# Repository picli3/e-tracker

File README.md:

# e-track

E-paper based GPS tracker PCB design using KiCad.

## Project Structure

- `e-track.kicad_pcb` - Main PCB layout
- `e-track.kicad_sch` - Schematic file
- `e-track.kicad_pro` - KiCad project file
- `e-track.kicad_prl` - KiCad layout settings
- `Power_Manager.kicad_sch` - Power management module
- `e-paper.kicad_sch` - E-paper display module
- `docs/` - Datasheets and documentation

## Features

- E-paper display interface
- GPS module integration
- Power management system

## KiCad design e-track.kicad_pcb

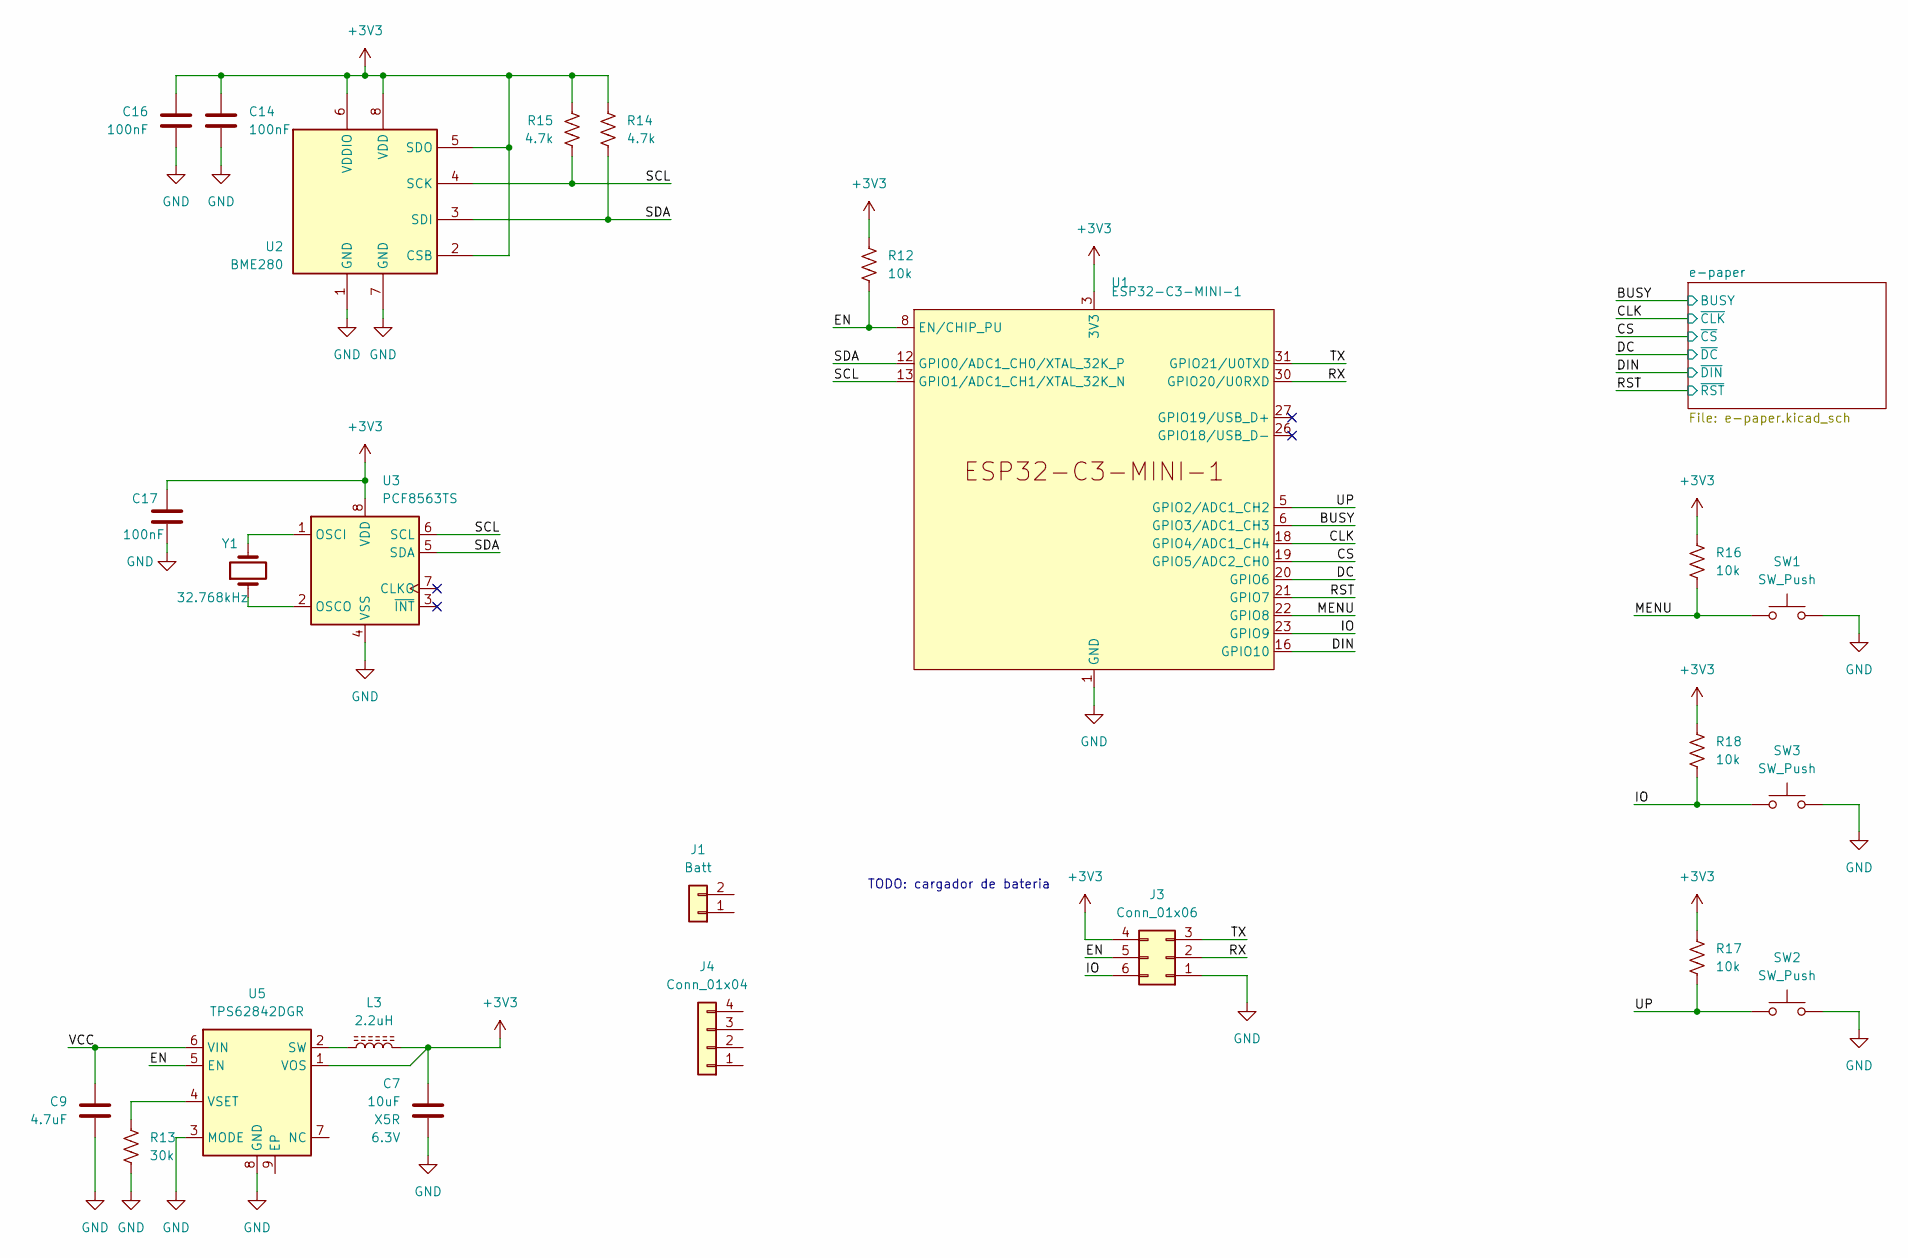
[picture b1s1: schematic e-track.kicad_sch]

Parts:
C7: 10uF; C_0805_2012Metric_Pad1.18x1.45mm_HandSolder; Mfr. Part CL21A106KPFNNNE; LCSC Part C17024
C9: 4.7uF; C_0603_1608Metric_Pad1.08x0.95mm_HandSolder; Mfr. Part CL10A475KP8NNNC; LCSC Part C1705
C14, C16, C17: 100nF; C_0603_1608Metric
J1: Batt; Samtec_UMPS-02-XX.X-X-V-S_1x02_P2.0mm_Socket
J3: Conn_01x06; pin-programmer
J4: Conn_01x04; pogo-pin-female-4P-2.54
L3: 2.2uH; L_Taiyo-Yuden_MD-4040; Mfr. Part LQH44PN2R2MP0L; LCSC Part C86081
R12, R16, R17, R18: 10k; R_0603_1608Metric
R13: 30k; R_0603_1608Metric_Pad0.98x0.95mm_HandSolder; Mfr. Part 0603WAF3002T5E; LCSC Part C22984
R14, R15: 4.7k; R_0603_1608Metric
SW1, SW2, SW3: SW_Push; SW_TL3340AF160QG
U1: ESP32-C3-MINI-1; ESP32-C3-MINI-1U
U2: BME280; Bosch_LGA-8_2.5x2.5mm_P0.65mm_ClockwisePinNumbering
U3: PCF8563TS; MSOP-8_3x3mm_P0.65mm; Part # PCF8563TS/5,118; LCSC C27397
U5: TPS62842DGR; MSOP-8-1EP_3x3mm_P0.65mm_EP1.5x1.8mm
Y1: 32.768kHz; Crystal_SMD_3215-2Pin_3.2x1.5mm; Part # SC-32S32.768kHz20PPM7pF; LCSC C97604

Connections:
+3V3: C7.1, C14.2, C16.2, C17.2, J3.4, L3.2, R12.2, R14.2, R15.2, R16.2, R17.2, R18.2, U1.3 (3V3), U2.2 (CSB), U2.5 (SDO), U2.6 (VDDIO), U2.8 (VDD), U3.8 (VDD), U5.1 (VOS); also elsewhere on the board
/BUSY: U1.6 (GPIO3/ADC1_CH3); also elsewhere on the board
/CLK: U1.18 (GPIO4/ADC1_CH4); also elsewhere on the board
/CS: U1.19 (GPIO5/ADC2_CH0); also elsewhere on the board
/DC: U1.20 (GPIO6); also elsewhere on the board
/DIN: U1.16 (GPIO10); also elsewhere on the board
/EN: J3.5, R12.1, U1.8 (EN/CHIP_PU), U5.5 (EN)
/IO: J3.6, R18.1, SW3.1, U1.23 (GPIO9)
/MENU: R16.1, SW1.1, U1.22 (GPIO8)
/RST: U1.21 (GPIO7); also elsewhere on the board
/RX: J3.2, U1.30 (GPIO20/U0RXD)
/SCL: R15.1, U1.13 (GPIO1/ADC1_CH1/XTAL_32K_N), U2.4 (SCK), U3.6 (SCL)
/SDA: R14.1, U1.12 (GPIO0/ADC1_CH0/XTAL_32K_P), U2.3 (SDI), U3.5 (SDA)
/TX: J3.3, U1.31 (GPIO21/U0TXD)
/UP: R17.1, SW2.1, U1.5 (GPIO2/ADC1_CH2)
/VCC: C9.1, U5.6 (VIN)
GND: C7.2, C9.2, C14.1, C16.1, C17.1, J3.1, R13.2, SW1.2, SW2.2, SW3.2, U1.1 (GND), U1.2 (GND), U1.11 (GND), U1.14 (GND), U1.36 (GND), U1.37 (GND), U1.38 (GND), U1.39 (GND), U1.40 (GND), U1.41 (GND), U1.42 (GND), U1.43 (GND), U1.44 (GND), U1.45 (GND), U1.46 (GND), U1.47 (GND), U1.48 (GND), U1.49 (GND), U1.50 (GND), U1.51 (GND), U1.52 (GND), U1.53 (GND), U2.1 (GND), U2.7 (GND), U3.4 (VSS), U5.3 (MODE), U5.8 (GND); also elsewhere on the board
unnamed: U3.1 (OSCI), Y1.2
unnamed: U3.2 (OSCO), Y1.1
unnamed: L3.1, U5.2 (SW)
unnamed: R13.1, U5.4 (VSET)

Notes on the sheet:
TODO: cargador de bateria

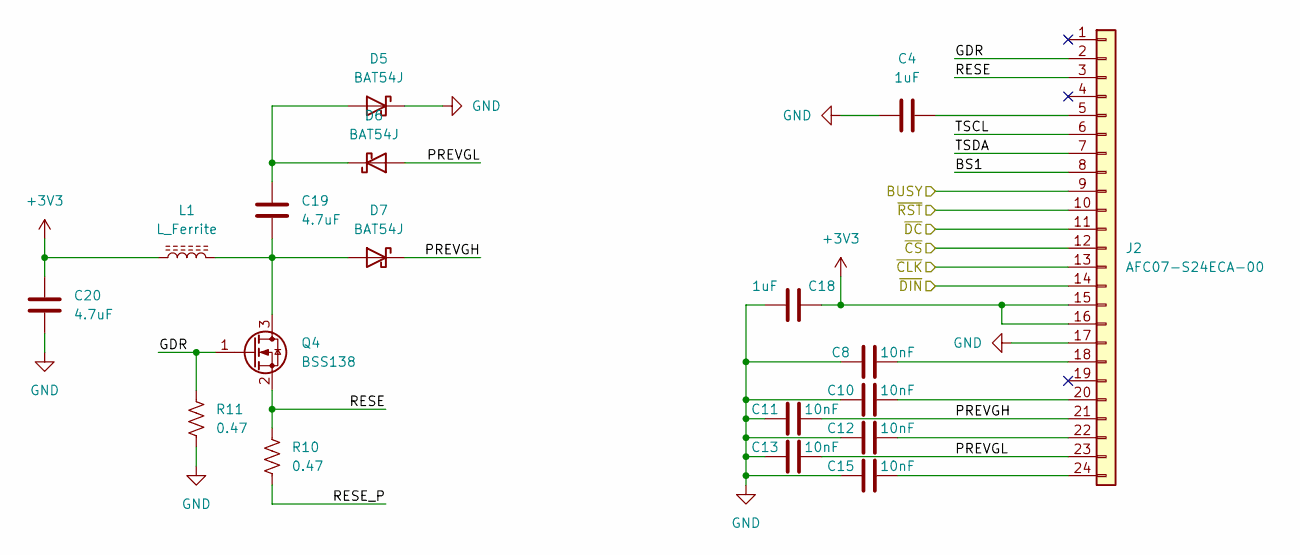
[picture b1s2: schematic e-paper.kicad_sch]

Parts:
C4, C18: 1uF; C_0603_1608Metric
C8, C10, C11, C12, C13, C15: 10nF; C_0603_1608Metric
C19, C20: 4.7uF; C_0603_1608Metric
D5, D6, D7: BAT54J; D_SOD-323F; LCSC C82046
J2: AFC07-S24ECA-00; TE_2-1734839-4_1x24-1MP_P0.5mm_Horizontal; Part # AFC07-S24ECA-00; LCSC C262643
L1: L_Ferrite; L_0805_2012Metric
Q4: BSS138; SOT-23
R10, R11: 0.47

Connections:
+3V3: C18.2, C20.1, J2.15, J2.16, L1.1; also elsewhere on the board
/BUSY: J2.9; also elsewhere on the board
/CLK: J2.13; also elsewhere on the board
/CS: J2.12; also elsewhere on the board
/DC: J2.11; also elsewhere on the board
/DIN: J2.14; also elsewhere on the board
/RST: J2.10; also elsewhere on the board
/e-paper/BS1: J2.8
/e-paper/GDR: J2.2, Q4.1 (G), R11.1
/e-paper/PREVGH: C11.2, D7.1 (K), J2.21
/e-paper/PREVGL: C13.2, D6.2 (A), J2.23
/e-paper/RESE: J2.3, Q4.2 (S), R10.1
/e-paper/TSCL: J2.6
/e-paper/TSDA: J2.7
GND: C4.1, C8.1, C10.1, C11.1, C12.1, C13.1, C15.1, C18.1, C20.2, D5.1 (K), J2.17, R11.2; also elsewhere on the board
unnamed: C19.1, D5.2 (A), D6.1 (K)
unnamed: C19.2, D7.2 (A), L1.2, Q4.3 (D)
unnamed: C4.2, J2.5
unnamed: C8.2, J2.18
unnamed: C10.2, J2.20
unnamed: C12.2, J2.22
unnamed: C15.2, J2.24

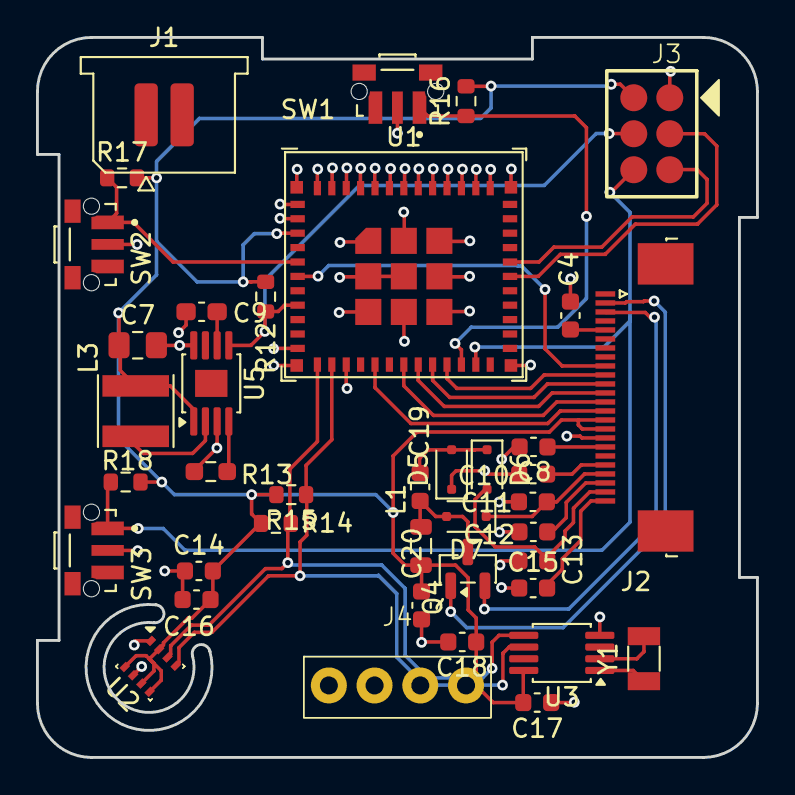
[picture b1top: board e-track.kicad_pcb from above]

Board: 2 copper layers, 40.0 x 40.0 mm, 40 parts (0 on the bottom side), 32 nets.

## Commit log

2026-06-04 Initial commit: e-track PCB project
2026-06-04 Add README
2026-06-04 Add PCB design screenshots
2026-06-04 Update PCB design and add SVG exports, improve gitignore
2026-06-09 agregando conector y RTC
2026-06-10 agregando page animada
2026-06-10 trigger pages rebuild
2026-06-10 move Pinion site to docs root for GitHub Pages
2026-06-10 fix Pinion source path to load spec.json
2026-06-10 agregando imagenes del docs
2026-06-10 fix Pinion source to absolute path for GitHub Pages assets
